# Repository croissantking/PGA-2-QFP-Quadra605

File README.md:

Quadra 605 PGA 68040 to QFP 68040 Adapter

Simple adapter to use a QFP CPU in a Quadra 605. NOTE: Orientation sensitive, please check if it will work in your machine.
Optional fan header and a jumper that can be cut to feed 3.3v instead (for use with a V suffix CPU). Will work with FPU-less CPUs also.

PGA-2-QFP (c) by zigzagjoe 2024

PGA-2-QFP is licensed under a
Creative Commons Attribution-NonCommercial 4.0 International License.

You should have received a copy of the license along with this
work. If not, see <https://creativecommons.org/licenses/by-nc/4.0/>.

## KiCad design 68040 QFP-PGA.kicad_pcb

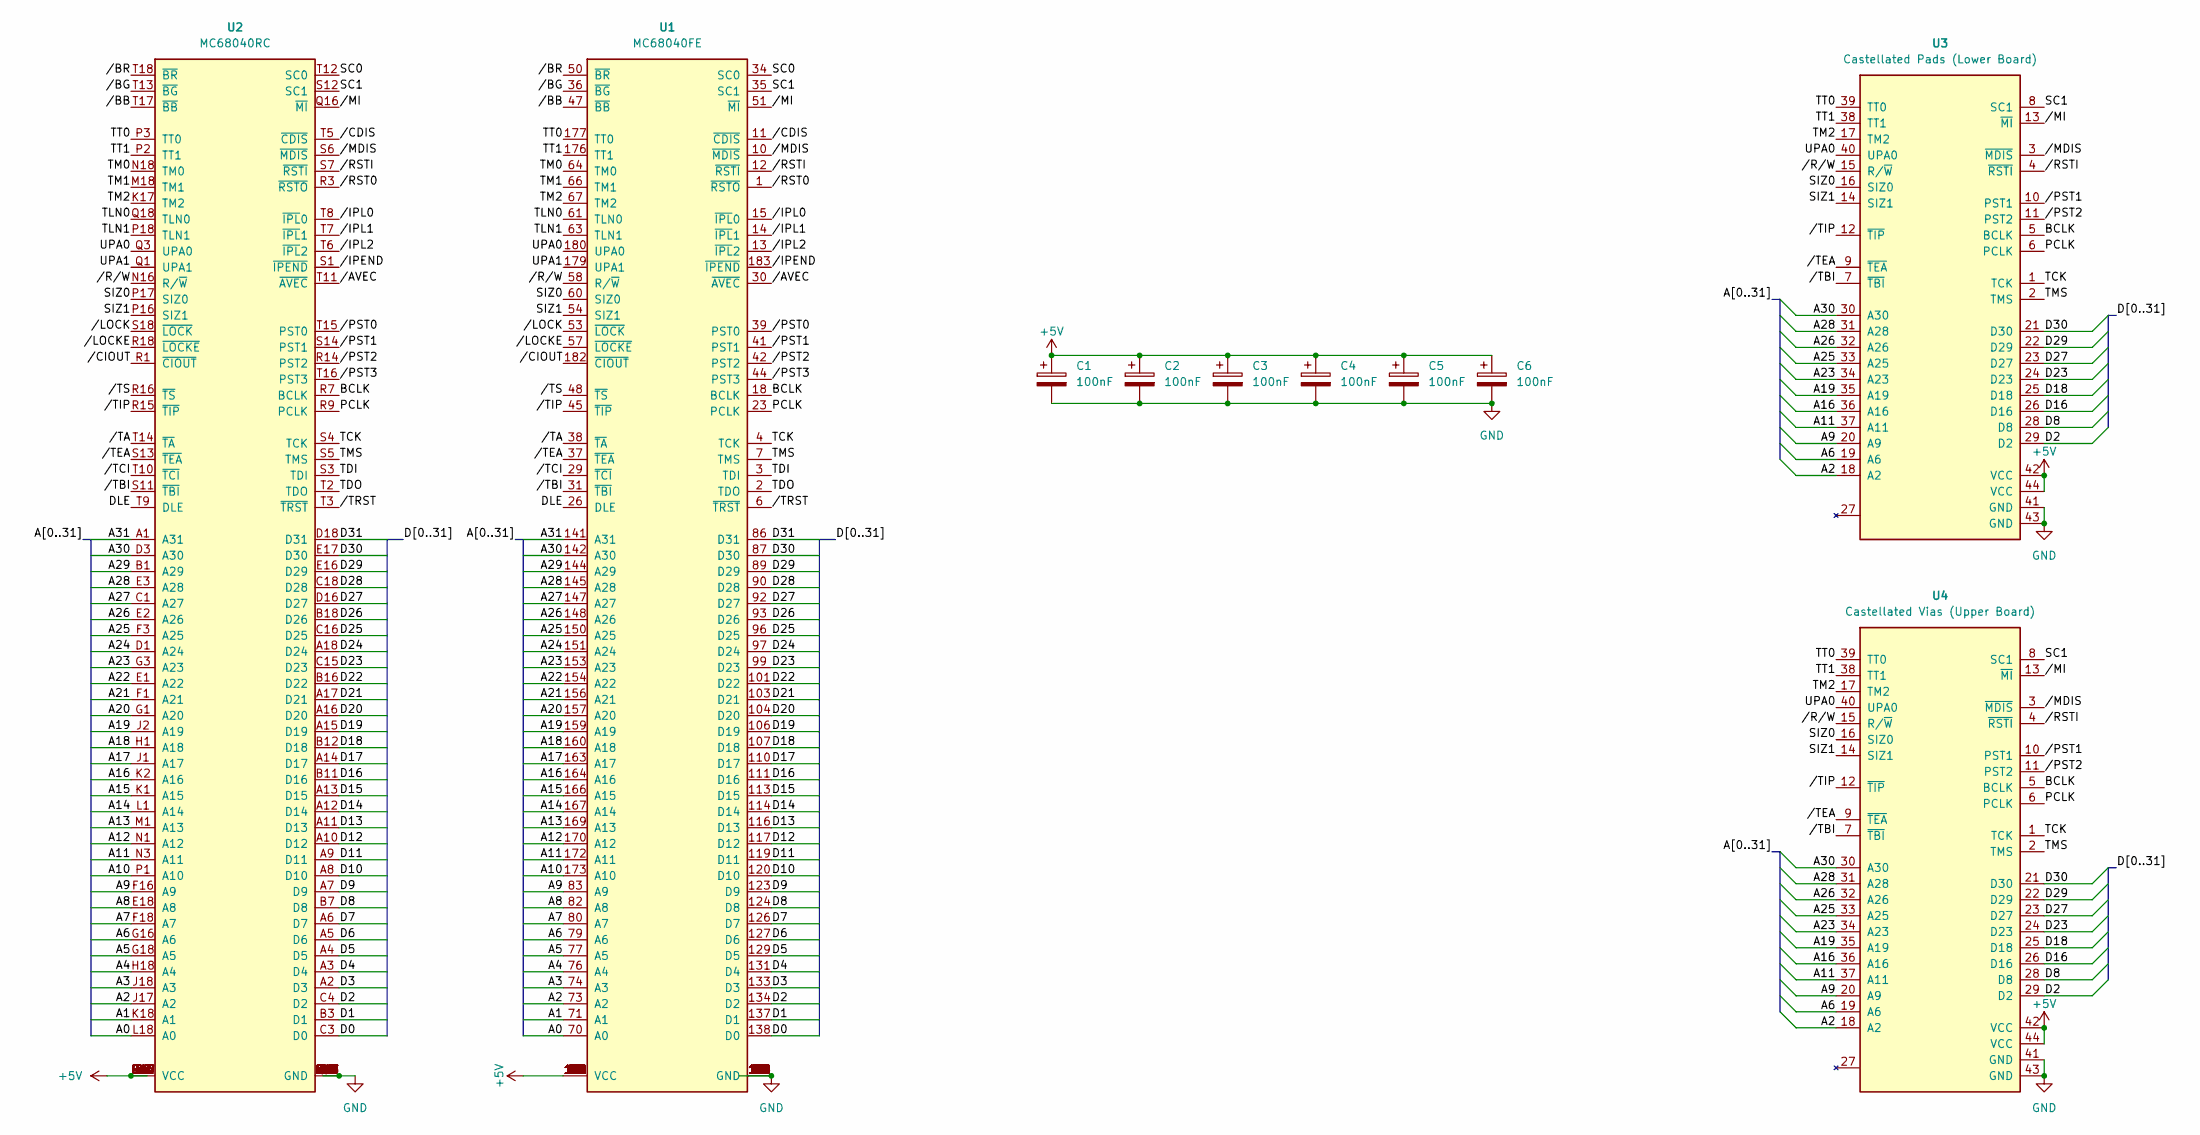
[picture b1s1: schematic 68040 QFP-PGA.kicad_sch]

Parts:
C1, C2, C3, C4, C5, C6: 100nF; C_0805_2012Metric; PartNumber CL21A226MAQNNNE; LCSC C45783
U1: MC68040FE; Mot_QFP184_Updated
U2: MC68040RC; PGA-179_1.1H-1.6R
U3: Castellated Pads (Lower Board); breakout_castellated_lower
U4: Castellated Vias (Upper Board); breakout_castellated_upper

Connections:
+5V: C1.1, C2.1, C3.1, C4.1, C5.1, C6.1, U1.9 (VCC), U1.19 (VCC), U1.21 (VCC), U1.32 (VCC), U1.43 (VCC), U1.49 (VCC), U1.56 (VCC), U1.62 (VCC), U1.69 (VCC), U1.75 (VCC), U1.81 (VCC), U1.88 (VCC), U1.94 (VCC), U1.100 (VCC), U1.102 (VCC), U1.109 (VCC), U1.115 (VCC), U1.122 (VCC), U1.128 (VCC), U1.136 (VCC), U1.143 (VCC), U1.149 (VCC), U1.155 (VCC), U1.161 (VCC), U1.168 (VCC), U1.175 (VCC), U1.181 (VCC), U2.B5 (VCC), U2.B9 (VCC), U2.B14 (VCC), U2.C2 (VCC), U2.C5 (VCC), U2.C8 (VCC), U2.C10 (VCC), U2.C12 (VCC), U2.C14 (VCC), U2.C17 (VCC), U2.G2 (VCC), U2.G17 (VCC), U2.H3 (VCC), U2.H16 (VCC), U2.J3 (VCC), U2.J16 (VCC), U2.L16 (VCC), U2.M2 (VCC), U2.M3 (VCC), U2.M17 (VCC), U2.R2 (VCC), U2.R5 (VCC), U2.R8 (VCC), U2.R12 (VCC), U2.R17 (VCC), U2.S8 (VCC), U2.S16 (VCC), U3.42 (VCC), U3.44 (VCC), U4.42 (VCC), U4.44 (VCC); also elsewhere on the board
/A0: U1.70 (A0), U2.L18 (A0); also elsewhere on the board
/A1: U1.71 (A1), U2.K18 (A1); also elsewhere on the board
/A2: U1.73 (A2), U2.J17 (A2), U3.18 (A2), U4.18 (A2)
/A3: U1.74 (A3), U2.J18 (A3); also elsewhere on the board
/A4: U1.76 (A4), U2.H18 (A4); also elsewhere on the board
/A5: U1.77 (A5), U2.G18 (A5); also elsewhere on the board
/A6: U1.79 (A6), U2.G16 (A6), U3.19 (A6), U4.19 (A6)
/A7: U1.80 (A7), U2.F18 (A7); also elsewhere on the board
/A8: U1.82 (A8), U2.E18 (A8); also elsewhere on the board
/A9: U1.83 (A9), U2.F16 (A9), U3.20 (A9), U4.20 (A9)
/A10: U1.173 (A10), U2.P1 (A10); also elsewhere on the board
/A11: U1.172 (A11), U2.N3 (A11), U3.37 (A11), U4.37 (A11)
/A12: U1.170 (A12), U2.N1 (A12); also elsewhere on the board
/A13: U1.169 (A13), U2.M1 (A13); also elsewhere on the board
/A14: U1.167 (A14), U2.L1 (A14); also elsewhere on the board
/A15: U1.166 (A15), U2.K1 (A15); also elsewhere on the board
/A16: U1.164 (A16), U2.K2 (A16), U3.36 (A16), U4.36 (A16)
/A17: U1.163 (A17), U2.J1 (A17); also elsewhere on the board
/A18: U1.160 (A18), U2.H1 (A18); also elsewhere on the board
/A19: U1.159 (A19), U2.J2 (A19), U3.35 (A19), U4.35 (A19)
/A20: U1.157 (A20), U2.G1 (A20); also elsewhere on the board
/A21: U1.156 (A21), U2.F1 (A21); also elsewhere on the board
/A22: U1.154 (A22), U2.E1 (A22); also elsewhere on the board
/A23: U1.153 (A23), U2.G3 (A23), U3.34 (A23), U4.34 (A23)
/A24: U1.151 (A24), U2.D1 (A24); also elsewhere on the board
/A25: U1.150 (A25), U2.F3 (A25), U3.33 (A25), U4.33 (A25)
/A26: U1.148 (A26), U2.E2 (A26), U3.32 (A26), U4.32 (A26)
/A27: U1.147 (A27), U2.C1 (A27); also elsewhere on the board
/A28: U1.145 (A28), U2.E3 (A28), U3.31 (A28), U4.31 (A28)
/A29: U1.144 (A29), U2.B1 (A29); also elsewhere on the board
/A30: U1.142 (A30), U2.D3 (A30), U3.30 (A30), U4.30 (A30)
/A31: U1.141 (A31), U2.A1 (A31); also elsewhere on the board
/BCLK: U1.18 (BCLK), U2.R7 (BCLK), U3.5 (BCLK), U4.5 (BCLK)
/D0: U1.138 (D0), U2.C3 (D0); also elsewhere on the board
/D1: U1.137 (D1), U2.B3 (D1); also elsewhere on the board
/D2: U1.134 (D2), U2.C4 (D2), U3.29 (D2), U4.29 (D2)
/D3: U1.133 (D3), U2.A2 (D3); also elsewhere on the board
/D4: U1.131 (D4), U2.A3 (D4); also elsewhere on the board
/D5: U1.129 (D5), U2.A4 (D5); also elsewhere on the board
/D6: U1.127 (D6), U2.A5 (D6); also elsewhere on the board
/D7: U1.126 (D7), U2.A6 (D7); also elsewhere on the board
/D8: U1.124 (D8), U2.B7 (D8), U3.28 (D8), U4.28 (D8)
/D9: U1.123 (D9), U2.A7 (D9); also elsewhere on the board
/D10: U1.120 (D10), U2.A8 (D10); also elsewhere on the board
/D11: U1.119 (D11), U2.A9 (D11); also elsewhere on the board
/D12: U1.117 (D12), U2.A10 (D12); also elsewhere on the board
/D13: U1.116 (D13), U2.A11 (D13); also elsewhere on the board
/D14: U1.114 (D14), U2.A12 (D14); also elsewhere on the board
/D15: U1.113 (D15), U2.A13 (D15); also elsewhere on the board
/D16: U1.111 (D16), U2.B11 (D16), U3.26 (D16), U4.26 (D16)
/D17: U1.110 (D17), U2.A14 (D17); also elsewhere on the board
/D18: U1.107 (D18), U2.B12 (D18), U3.25 (D18), U4.25 (D18)
/D19: U1.106 (D19), U2.A15 (D19); also elsewhere on the board
/D20: U1.104 (D20), U2.A16 (D20); also elsewhere on the board
/D21: U1.103 (D21), U2.A17 (D21); also elsewhere on the board
/D22: U1.101 (D22), U2.B16 (D22); also elsewhere on the board
/D23: U1.99 (D23), U2.C15 (D23), U3.24 (D23), U4.24 (D23)
/D24: U1.97 (D24), U2.A18 (D24); also elsewhere on the board
/D25: U1.96 (D25), U2.C16 (D25); also elsewhere on the board
/D26: U1.93 (D26), U2.B18 (D26); also elsewhere on the board
/D27: U1.92 (D27), U2.D16 (D27), U3.23 (D27), U4.23 (D27)
/D28: U1.90 (D28), U2.C18 (D28); also elsewhere on the board
/D29: U1.89 (D29), U2.E16 (D29), U3.22 (D29), U4.22 (D29)
/D30: U1.87 (D30), U2.E17 (D30), U3.21 (D30), U4.21 (D30)
/D31: U1.86 (D31), U2.D18 (D31); also elsewhere on the board
/DLE: U1.26 (DLE), U2.T9 (DLE); also elsewhere on the board
/PCLK: U1.23 (PCLK), U2.R9 (PCLK), U3.6 (PCLK), U4.6 (PCLK)
/SC0: U1.34 (SC0), U2.T12 (SC0); also elsewhere on the board
/SC1: U1.35 (SC1), U2.S12 (SC1), U3.8 (SC1), U4.8 (SC1)
/SIZ0: U1.60 (SIZ0), U2.P17 (SIZ0), U3.16 (SIZ0), U4.16 (SIZ0)
/SIZ1: U1.54 (SIZ1), U2.P16 (SIZ1), U3.14 (SIZ1), U4.14 (SIZ1)
/TCK: U1.4 (TCK), U2.S4 (TCK), U3.1 (TCK), U4.1 (TCK)
/TDI: U1.3 (TDI), U2.S3 (TDI); also elsewhere on the board
/TDO: U1.2 (TDO), U2.T2 (TDO); also elsewhere on the board
/TLN0: U1.61 (TLN0), U2.Q18 (TLN0); also elsewhere on the board
/TLN1: U1.63 (TLN1), U2.P18 (TLN1); also elsewhere on the board
/TM0: U1.64 (TM0), U2.N18 (TM0); also elsewhere on the board
/TM1: U1.66 (TM1), U2.M18 (TM1); also elsewhere on the board
/TM2: U1.67 (TM2), U2.K17 (TM2), U3.17 (TM2), U4.17 (TM2)
/TMS: U1.7 (TMS), U2.S5 (TMS), U3.2 (TMS), U4.2 (TMS)
/TT0: U1.177 (TT0), U2.P3 (TT0), U3.39 (TT0), U4.39 (TT0)
/TT1: U1.176 (TT1), U2.P2 (TT1), U3.38 (TT1), U4.38 (TT1)
/UPA0: U1.180 (UPA0), U2.Q3 (UPA0), U3.40 (UPA0), U4.40 (UPA0)
/UPA1: U1.179 (UPA1), U2.Q1 (UPA1); also elsewhere on the board
//AVEC: U1.30 (~AVEC), U2.T11 (~AVEC); also elsewhere on the board
//BB: U1.47 (~BB), U2.T17 (~BB); also elsewhere on the board
//BG: U1.36 (~BG), U2.T13 (~BG); also elsewhere on the board
//BR: U1.50 (~BR), U2.T18 (~BR); also elsewhere on the board
//CDIS: U1.11 (~CDIS), U2.T5 (~CDIS); also elsewhere on the board
//CIOUT: U1.182 (~CIOUT), U2.R1 (~CIOUT); also elsewhere on the board
//IPEND: U1.183 (~IPEND), U2.S1 (~IPEND); also elsewhere on the board
//IPL0: U1.15 (~IPL0), U2.T8 (~IPL0); also elsewhere on the board
//IPL1: U1.14 (~IPL1), U2.T7 (~IPL1); also elsewhere on the board
//IPL2: U1.13 (~IPL2), U2.T6 (~IPL2); also elsewhere on the board
//LOCK: U1.53 (~LOCK), U2.S18 (~LOCK); also elsewhere on the board
//LOCKE: U1.57 (~LOCKE), U2.R18 (~LOCKE); also elsewhere on the board
//MDIS: U1.10 (~MDIS), U2.S6 (~MDIS), U3.3 (~MDIS), U4.3 (~MDIS)
//MI: U1.51 (~MI), U2.Q16 (~MI), U3.13 (~MI), U4.13 (~MI)
//PST0: U1.39 (PST0), U2.T15 (PST0); also elsewhere on the board
//PST1: U1.41 (PST1), U2.S14 (PST1), U3.10 (PST1), U4.10 (PST1)
//PST2: U1.42 (PST2), U2.R14 (PST2), U3.11 (PST2), U4.11 (PST2)
//PST3: U1.44 (PST3), U2.T16 (PST3); also elsewhere on the board
//RST0: U1.1 (~RSTO), U2.R3 (~RSTO); also elsewhere on the board
//RSTI: U1.12 (~RSTI), U2.S7 (~RSTI), U3.4 (~RSTI), U4.4 (~RSTI)
//R/W: U1.58 (R/~W), U2.N16 (R/~W), U3.15 (R/~W), U4.15 (R/~W)
//TA: U1.38 (~TA), U2.T14 (~TA); also elsewhere on the board
//TBI: U1.31 (~TBI), U2.S11 (~TBI), U3.7 (~TBI), U4.7 (~TBI)
//TCI: U1.29 (~TCI), U2.T10 (~TCI); also elsewhere on the board
//TEA: U1.37 (~TEA), U2.S13 (~TEA), U3.9 (~TEA), U4.9 (~TEA)
//TIP: U1.45 (~TIP), U2.R15 (~TIP), U3.12 (~TIP), U4.12 (~TIP)
//TRST: U1.6 (~TRST), U2.T3 (~TRST); also elsewhere on the board
//TS: U1.48 (~TS), U2.R16 (~TS); also elsewhere on the board
GND: C1.2, C2.2, C3.2, C4.2, C5.2, C6.2, U1.5 (GND), U1.8 (GND), U1.16 (GND), U1.17 (GND), U1.20 (GND), U1.22 (GND), U1.24 (GND), U1.25 (GND), U1.27 (GND), U1.28 (GND), U1.33 (GND), U1.40 (GND), U1.46 (GND), U1.52 (GND), U1.55 (GND), U1.59 (GND), U1.65 (GND), U1.68 (GND), U1.72 (GND), U1.78 (GND), U1.84 (GND), U1.85 (GND), U1.91 (GND), U1.95 (GND), U1.98 (GND), U1.105 (GND), U1.108 (GND), U1.112 (GND), U1.118 (GND), U1.121 (GND), U1.125 (GND), U1.130 (GND), U1.132 (GND), U1.135 (GND), U1.139 (GND), U1.140 (GND), U1.146 (GND), U1.152 (GND), U1.158 (GND), U1.162 (GND), U1.165 (GND), U1.171 (GND), U1.174 (GND), U1.178 (GND), U1.184 (GND), U2.B2 (GND), U2.B4 (GND), U2.B6 (GND), U2.B8 (GND), U2.B10 (GND), U2.B13 (GND), U2.B15 (GND), U2.B17 (GND), U2.C6 (GND), U2.C7 (GND), U2.C9 (GND), U2.C11 (GND), U2.C13 (GND), U2.D2 (GND), U2.D17 (GND), U2.F2 (GND), U2.F17 (GND), U2.H2 (GND), U2.H17 (GND), U2.K3 (GND), U2.K16 (GND), U2.L2 (GND), U2.L3 (GND), U2.L17 (GND), U2.M16 (GND), U2.N2 (GND), U2.N17 (GND), U2.Q2 (GND), U2.Q17 (GND), U2.R4 (GND), U2.R6 (GND), U2.R10 (GND), U2.R11 (GND), U2.R13 (GND), U2.S2 (GND), U2.S9 (GND), U2.S10 (GND), U2.S15 (GND), U2.S17 (GND), U2.T4 (GND), U3.41 (GND), U3.43 (GND), U4.41 (GND), U4.43 (GND); also elsewhere on the board

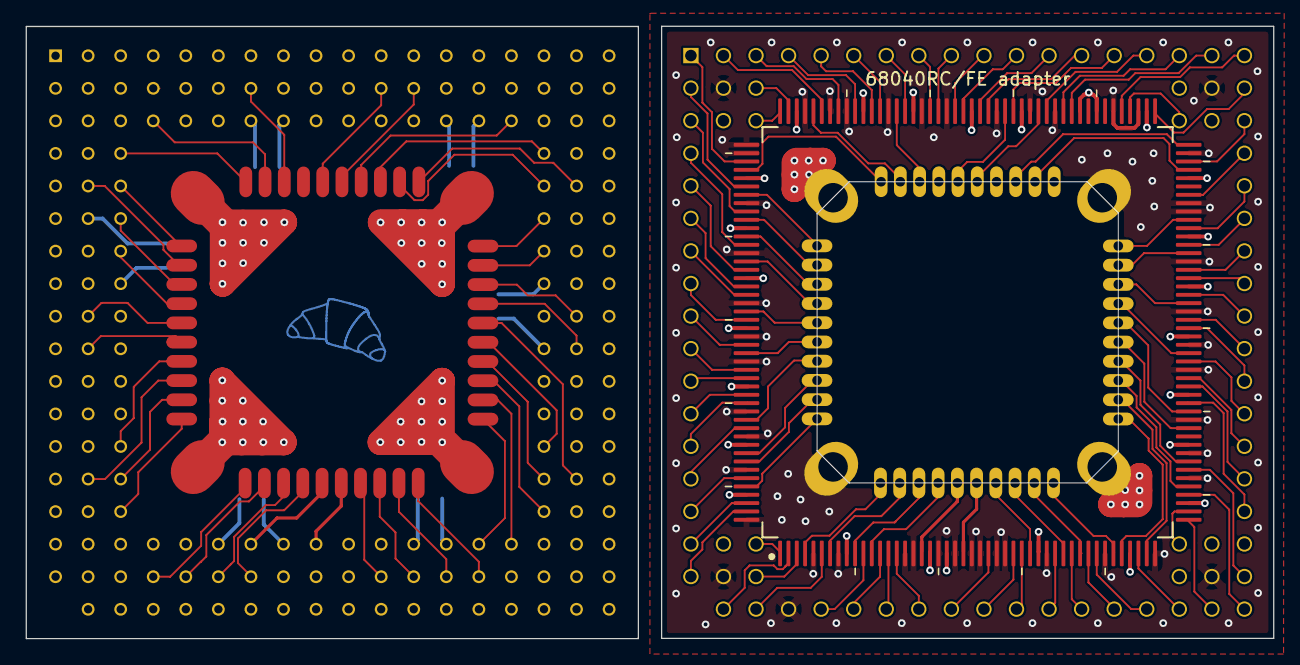
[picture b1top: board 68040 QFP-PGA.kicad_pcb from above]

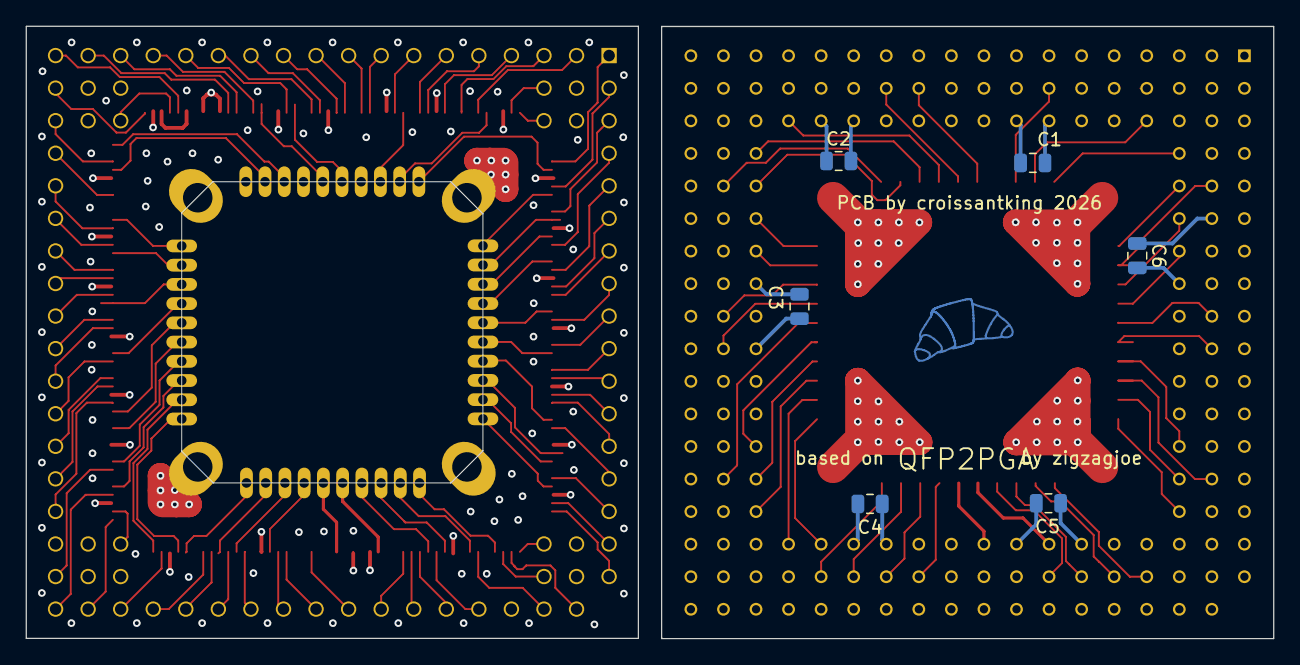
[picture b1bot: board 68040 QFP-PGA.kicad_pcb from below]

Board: 4 copper layers, 97.3 x 47.8 mm, 11 parts (6 on the bottom side), 114 nets.

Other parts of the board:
U2#2: MC68040RC; PGA-179_1.1H-1.6R

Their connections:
+5V: U2#2.C2 (VCC), U2#2.C17 (VCC), U2#2.R2 (VCC), U2#2.R17 (VCC), U2#2.S16 (VCC); also elsewhere on the board
/A0: U2#2.L18 (A0); also elsewhere on the board
/A1: U2#2.K18 (A1); also elsewhere on the board
/A3: U2#2.J18 (A3); also elsewhere on the board
/A4: U2#2.H18 (A4); also elsewhere on the board
/A5: U2#2.G18 (A5); also elsewhere on the board
/A7: U2#2.F18 (A7); also elsewhere on the board
/A8: U2#2.E18 (A8); also elsewhere on the board
/A10: U2#2.P1 (A10); also elsewhere on the board
/A12: U2#2.N1 (A12); also elsewhere on the board
/A13: U2#2.M1 (A13); also elsewhere on the board
/A14: U2#2.L1 (A14); also elsewhere on the board
/A15: U2#2.K1 (A15); also elsewhere on the board
/A17: U2#2.J1 (A17); also elsewhere on the board
/A18: U2#2.H1 (A18); also elsewhere on the board
/A20: U2#2.G1 (A20); also elsewhere on the board
/A21: U2#2.F1 (A21); also elsewhere on the board
/A22: U2#2.E1 (A22); also elsewhere on the board
/A24: U2#2.D1 (A24); also elsewhere on the board
/A27: U2#2.C1 (A27); also elsewhere on the board
/A29: U2#2.B1 (A29); also elsewhere on the board
/A31: U2#2.A1 (A31); also elsewhere on the board
/D0: U2#2.C3 (D0); also elsewhere on the board
/D1: U2#2.B3 (D1); also elsewhere on the board
/D3: U2#2.A2 (D3); also elsewhere on the board
/D4: U2#2.A3 (D4); also elsewhere on the board
/D5: U2#2.A4 (D5); also elsewhere on the board
/D6: U2#2.A5 (D6); also elsewhere on the board
/D7: U2#2.A6 (D7); also elsewhere on the board
/D9: U2#2.A7 (D9); also elsewhere on the board
/D10: U2#2.A8 (D10); also elsewhere on the board
/D11: U2#2.A9 (D11); also elsewhere on the board
/D12: U2#2.A10 (D12); also elsewhere on the board
/D13: U2#2.A11 (D13); also elsewhere on the board
/D14: U2#2.A12 (D14); also elsewhere on the board
/D15: U2#2.A13 (D15); also elsewhere on the board
/D17: U2#2.A14 (D17); also elsewhere on the board
/D19: U2#2.A15 (D19); also elsewhere on the board
/D20: U2#2.A16 (D20); also elsewhere on the board
/D21: U2#2.A17 (D21); also elsewhere on the board
/D22: U2#2.B16 (D22); also elsewhere on the board
/D24: U2#2.A18 (D24); also elsewhere on the board
/D25: U2#2.C16 (D25); also elsewhere on the board
/D26: U2#2.B18 (D26); also elsewhere on the board
/D28: U2#2.C18 (D28); also elsewhere on the board
/D31: U2#2.D18 (D31); also elsewhere on the board
/DLE: U2#2.T9 (DLE); also elsewhere on the board
/SC0: U2#2.T12 (SC0); also elsewhere on the board
/TDI: U2#2.S3 (TDI); also elsewhere on the board
/TDO: U2#2.T2 (TDO); also elsewhere on the board
/TLN0: U2#2.Q18 (TLN0); also elsewhere on the board
/TLN1: U2#2.P18 (TLN1); also elsewhere on the board
/TM0: U2#2.N18 (TM0); also elsewhere on the board
/TM1: U2#2.M18 (TM1); also elsewhere on the board
/UPA1: U2#2.Q1 (UPA1); also elsewhere on the board
//AVEC: U2#2.T11 (~AVEC); also elsewhere on the board
//BB: U2#2.T17 (~BB); also elsewhere on the board
//BG: U2#2.T13 (~BG); also elsewhere on the board
//BR: U2#2.T18 (~BR); also elsewhere on the board
//CDIS: U2#2.T5 (~CDIS); also elsewhere on the board
//CIOUT: U2#2.R1 (~CIOUT); also elsewhere on the board
//IPEND: U2#2.S1 (~IPEND); also elsewhere on the board
//IPL0: U2#2.T8 (~IPL0); also elsewhere on the board
//IPL1: U2#2.T7 (~IPL1); also elsewhere on the board
//IPL2: U2#2.T6 (~IPL2); also elsewhere on the board
//LOCK: U2#2.S18 (~LOCK); also elsewhere on the board
//LOCKE: U2#2.R18 (~LOCKE); also elsewhere on the board
//PST0: U2#2.T15 (PST0); also elsewhere on the board
//PST3: U2#2.T16 (PST3); also elsewhere on the board
//RST0: U2#2.R3 (~RSTO); also elsewhere on the board
//TA: U2#2.T14 (~TA); also elsewhere on the board
//TCI: U2#2.T10 (~TCI); also elsewhere on the board
//TRST: U2#2.T3 (~TRST); also elsewhere on the board
//TS: U2#2.R16 (~TS); also elsewhere on the board
GND: U2#2.B2 (GND), U2#2.B17 (GND), U2#2.S2 (GND), U2#2.S17 (GND), U2#2.T4 (GND); also elsewhere on the board
